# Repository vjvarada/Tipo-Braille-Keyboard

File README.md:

# What is a Braille KeyPad ?

- Braille KeyPad is a Bluetooth keyboard with a special layout that allows visually impaired individuals to easily navigate and type into SmartPhones and tablets. 
- There are 6 circular Braille input buttons on KeyPad arranged in a braille layout. By pressing combinations of the braille input buttons you can input text and symbols. Braille text input is compliant to UEB Grade 1 and Grade 2 braille except non-ASCII characters and some lower groupsigns & wordsigns.

# Physical Leyout:

- The braille keypads is a rectangular slab with rounded edges. It has all the buttons on one side, and is flat on the other.
- There is a slot for lanyard/wrist straps on one side of the rectangle. 
- Braille KeyPad consists of 6 circular "Braille" keys, 5 square "Special Keys" and a 5-Way Navigation stick with Center click.
- The 6 circular braille keys are used to input text and symbols by brailling in UEB grade 1 and grade 2 braille, in addition to long pressing the braille buttons of certain alphabets to trigger shortcuts on the SmartPhone/Tablet
- The 5 square keys are Alt, Ctrl, Shift, Space & Delete keys.
- The Navigation stick controls up, Down, Left, and Right.
- Clicking the center of the navigation stick represents enter/newline
- The bottom os the device has the ON/OFF slider and the USB Charging input.

# How to use
- Braille KeyPad is held between your palms, with the buttons facing away, and the flat side towards you. 

# Implementation:
How the HID Keypad is implemented for use with Braille

## Grade 1 Braille
The Braille Alphabet—Internationally Standardised
The letters a-z are common and standard for most braille country tables.

Grade 1 braille is a letter-for-letter substitution of its printed counterpart. This is the preferred code for beginners because it allows people to get familiar with, and recognize different aspects of, the code while learning how to read braille. 

English grade 1 braille consists of the 26 standard letters of the alphabet as well as punctuation.
### Charecters

| CHARACTER   |      BRAILLE      |  BRAILLE DOT/BUTTON # |
|----------|:-------------:|------:|
| letter sign | ⠰ | 56|
| a |	    ⠁	    | 1 |
| b |	    ⠃	    | 12 |
| c |	    ⠉	    | 14 |
| d |	    ⠙	    | 145 |
| e |	    ⠑	    | 15 |
| f |	    ⠋	    | 124 |
| g |	    ⠛	    | 1245 |
| h |	    ⠓	    | 125 |
| i |	    ⠊	    | 24 |
| j |	    ⠚	    | 245 |
| k |	    ⠅	    | 13 |
| l |	    ⠇	    | 123 |
| m |	    ⠍	    | 134 |
| n |	    ⠝	    | 1345 |
| o |	    ⠕	    | 135 |
| p |	    ⠏	    | 1234 |
| q |	    ⠟	    | 12345 |
| r |	    ⠗	    |1235 |
| s |	    ⠎	    | 234 |
| t |	    ⠞	    | 2345 |
| u |	    ⠥	    | 136 |
| v |	    ⠧	    | 1236 |
| w |	    ⠺	    | 2456 | 
| x |	    ⠭	    | 1346 |
| y |	    ⠽	    | 13456 |
| z |	    ⠵	    | 1356 |

### Numbers

| CHARACTER   |      BRAILLE      |  BRAILLE DOT/BUTTON # |
|----------|:-------------:|------:|
| number indicator |	⠼ 	| 3456 |
| 1 | 	⠼⠁	| 3456 1 |
| 2 |	⠼⠃	| 3456 12 |
| 3 |	⠼⠉	| 3456 14 |
| 4 |	⠼⠙	| 3456 145 |
| 5 |	⠼⠑	| 3456 15 |
| 6 |	⠼⠋	| 3456 124 |
| 7 |	⠼⠛	| 3456 1245 |
| 8 |	⠼⠓	| 3456 125 |
| 9 |	⠼⠊	| 3456 24 |
| 0 |	⠼⠚	| 3456 245 |

The number indicator (⠼) is placed before the first digit in a group. Space, hyphen, grade 1 indicator or clears it

Example:
```
100: 	⠼⠁⠚⠚

using Grade 1 indicator/Letter sign (⠰) to specify end of number
221b:	⠼⠃⠃⠁⠰⠃

```

### Punctuation

| CHARACTER   |      BRAILLE      |  BRAILLE DOT/BUTTON # |
|----------|:-------------:|------:|
|,|                     ⠂   |2|
|;|                  	⠆   |23|
|:|                    	⠒   |25|
|.(Period)|             ⠲   |256|
|?|     	            ⠦   |236|
|!|                     ⠖   |235|
|apostrophe '|          ⠄   |3|
|quote " |              ⠴   |356|
|hyphen - |             ⠤   |36|

### Symbols

| CHARACTER   |      BRAILLE      |  BRAILLE DOT/BUTTON # |
|----------|:-------------:|------:|
| & |	                 ⠈⠯	    | 4 12346|
| * |	                 ⠐⠔	    | 5 35|
| # |                    ⠸⠹        | 456 1456|
| @	|                    ⠈⠁        | 4 1|
| %	|                    ⠨⠴	    | 46 356|
| +	|                    ⠐⠖	    | 5 235|
| − (minus) |            ⠐⠤	    | 5 36|
| =	|                    ⠐⠶	    | 5 2356|
| ~ |                    ⠈⠔        | 4 35 |
| ` |                    ⠘⠡        | 45 16
| ^ |                    ⠈⠢        |4 26 |
| Underscore _ |         ⠨⠤        |46 36|
| Verical Line |         ⠸⠳        |456 1256| 
| / |                    ⠸⠌        |456 34|
| \ |                    ⠸⠡        |456 16|
| ( |                    ⠐⠣        |5 126|
| ) |                    ⠐⠜        |5 345|
| [ |                    ⠨⠣        |46 126|
| ] |                    ⠨⠜        |46 345|
| { |                    ⠸⠣        |456 126|
| } |                    ⠸⠜        |456 345|
| < |                    ⠈⠣        |4 126|
| > |                    ⠈⠜        |4 345|
| $ |                    ⠈⠎        |4 234 |
| " |                    ⠠⠶        |6 2346 |

### Indicators

| CHARACTER   |      BRAILLE      |  BRAILLE DOT/BUTTON # |
|----------|:-------------:|------:|
| number indicator |                	⠼    	| 3456 |
| grade 1 letter indicator |           ⠰	    | 56|
| grade 1 word indicator |             ⠰⠰	    | 56 56|
| grade 1 lock indicator |             ⠰⠰⠰	    | 56 56|
| grade 1 terminator indicator |       ⠰⠄	    | 56 3|
| capital letter indicator |           ⠠	    | 6|
| capital word indicator |             ⠠⠠      | 6 6|
| capital lock indicator |             ⠠⠠⠠     | 6 6 6|
| capital terminator indicator |       ⠠⠄      | 6 3|

```
The capital(ization) sign ⠠ marks the first letter of a word as capitalized. 
It may occur in the middle of a word for camel case, as in the name deAngelo. 
It is doubled to place a word in all caps; this must be repeated for each word of an all-cap text.
Use ⠠⠠ to Capitalise proceeding charecter, ⠠⠠ to Capitalise a full word,
⠠⠠⠠ to capitalise a full passage and ⠠⠄ to terminate. Using space/hyphen 
etc resets to normal unless not using paragraph caps. 
Warning: ⠠⠺⠁⠗⠝⠊⠝⠛
WARNING: ⠠⠠⠺⠁⠗⠝⠊⠝⠛
```

```
Note: The letter sign (grade 1 symbol indicator) ⠰ is used to force the end of a series of numbers.
For example, ⠙⠁ ⟨da⟩ preceded by a number sign, ⠼⠙⠁, is read as 41. 
If instead 4a is intended (as in a section or apartment number), 
then the letter sign is used to force a reading of a rather than 1 for the final character: ⠼⠙⠰⠁ ⟨4a⟩.

It is also used to mark a character as standing for a letter rather than for a word. For example, ⠃ ⟨b⟩ on its own is normally read as the word but;
to indicate that it is instead the letter b, the letter sign is used: ⠰⠃ b. Plurals of letters (mind your ps and qs)
always use an apostrophe in braille, but other derivations may not, as in ⠰⠝⠹ nth [time]: ⠠⠎⠬ is Sing, ⠰⠠⠎⠬ is S-ing/Essing. The letter sign is also used to mark lower-case Roman numbers, as in ⠰⠊⠊⠊ ⟨iii⟩.
 ```
## Grade 2 Braille 

The literary braille code, grade 2, uses “contractions” that substitute shorter sequences for the full spelling of commonly-occurring letter groups. The contractions are similar to English print contractions, like “cannot” versus “can’t”, in the way that a word is shortened. For example, “the” is usually a single character in braille. 
Grade 2 braille is the most commonly used form of braille code and is found in books, public signage, and restaurant menus to name a few. It consists of the 26 standard letters of the alphabet, punctuation, and contractions.

```
letter sign  (⠰) used to mark a character as standing for a letter rather than for a word. For example,
 ⠃ ⟨b⟩ on its own is normally read as the word but; to indicate that it is instead the letter b, 
the letter sign is used: ⠰⠃ b. Plurals of letters (mind your ps and qs) always use an apostrophe in braille,
but other derivations may not, as in ⠰⠝⠹ nth [time]: ⠠⠎⠬ is Sing, ⠰⠠⠎⠬ is S-ing/Essing.[27] The letter sign 
is also used to mark lower-case Roman numbers, as in ⠰⠊⠊⠊ ⟨iii⟩.
```
### Alphabetic Wordsigns

| CHARACTER   | WORD    |      BRAILLE      |  BRAILLE DOT/BUTTON # |
|----------|:-------------:|:-------------:|------:|
| b | but |	            ⠃	    | 12 |
| c | can |	            ⠉	    | 14 |
| d | do |	            ⠙	    | 145 |
| e | every|            ⠑	    | 15 |
| f | from |            ⠋	    | 124 |
| g | go |              ⠛	    | 1245 |
| h | have |            ⠓	    | 125 |
| j | just |            ⠚	    | 245 |
| k | knowledge |	    ⠅	    | 13 |
| l | like |	        ⠇	    | 123 |
| m | more |	        ⠍	    | 134 |
| n | not |	            ⠝	    | 1345 |
| p | people |	        ⠏	    | 1234 |
| q | quite |	        ⠟	    | 12345 |
| r | rather |	        ⠗	    |1235 |
| s | so |	            ⠎	    | 234 |
| t | that |	        ⠞	    | 2345 |
| u | us |	            ⠥	    | 136 |
| v | very |	        ⠧	    | 1236 |
| w | will |	        ⠺	    | 2456 | 
| x | it |	            ⠭	    | 1346 |
| y | you |	            ⠽	    | 13456 |
| z | as |	            ⠵	    | 1356 |

### Strong Contractions (Part and Whole Word)

| CHARACTER   |      BRAILLE      |  BRAILLE DOT/BUTTON # |
|----------|:-------------:|------:|
| and |	    ⠯	    | 12346 |
| for |	    ⠿	    | 123456 |
| of |	    ⠷	    | 12356 |
| the |	    ⠮	    | 2346 |
| with |    ⠾	    | 23456 |

### Strong Wordsigns

| CHARACTER   |      BRAILLE      |  BRAILLE DOT/BUTTON # |
|----------|:-------------:|------:|
| child |	    ⠡	    | 16 |
| shall |	    ⠩	    | 146 |
| this |	    ⠹	    | 1456 |
| which |	    ⠱	    | 156 |
| out |	        ⠳	    | 1256 |
| still |	    ⠌	    | 34 |

isStandingAlone?

### Strong Groupsigns

| CHARACTER   |      BRAILLE      |  BRAILLE DOT/BUTTON # | Note |
|----------|:-------------:|:------:|------:|
| -ch- |	    ⠡	    | 16 | Letter join on either side|
| -sh- |	    ⠩	    | 146 |Letter join on either side|
| -th- |        ⠹	    | 1456 |Letter join on either side|
| -wh- |	    ⠱	    | 156 |Letter join on either side|
| -ou- |	    ⠳	    | 1256 |Letter join on either side|
| -st- |	    ⠌	    | 34 |Letter join on either side|
|------|----------------|----| -------------------------|
| gh |	        ⠣	    | 126 |
| ed |	        ⠫	    | 1246 |
| er |	        ⠻	    | 12456 |
| ow |          ⠪	    | 246 |
| ar |  	    ⠜	    | 345 |
| -ing |	    ⠬	    | 346 |Letter join on one side only, cannot be used to start a word|

### Lower Groupsigns

| CHARACTER   |      BRAILLE      |  BRAILLE DOT/BUTTON # | Note |
|----------|:-------------:|:------:|------:|
| -ea- |      ⠂	    | 2|Letters join on both side|
| -bb- |      ⠆	    | 23 |Letters join on both side|
| -cc- |      ⠒	    | 25 |Letters join on both side|
| -ff- |	  ⠖	    | 235 |Letters join on both side|
| -gg- |      ⠶	    | 2356 |Letters join on both side|
|------|----------------|----| -------------------------|
| be- |	      ⠆	    | 23 | |
| con- |	  ⠒	    | 25 |Letters join on one side only |
| dis- |	  ⠲	    | 256 |Letters join on one side only |
| -en- |	  ⠢	    | 26 |Letter join on either side|
| in |	      ⠔	    | 35 | |

### Lower Wordsigns

| CHARACTER   |      BRAILLE      |  BRAILLE DOT/BUTTON # |
|----------|:-------------:|------:|
| be |      ⠆	    | 23 |
| enough |  ⠢	    | 26 |
| were |    ⠶	    | 2356 |
| his |	    ⠦	    | 236 |
| in |	    ⠔	    | 35 |
| was |	    ⠴	    | 356 |

### Initial Letter Contractions

| CHARACTER   |      BRAILLE      |  BRAILLE DOT/BUTTON # |
|----------|:-------------:|------:|
|    day |  |5 145
|   ever |  |5 15
|  father | |5 124
|    here | |5 125
|    know | |5 13
|    lord | |5 123
|    mother |   |5 134
|    name | |5 1345
|    one |  |5 135
|    part | |5 1234
|    question | |5 12345
|    right |    |5 1235
|    some | |5 234
|    time | |5 2345
|    under | |5 136
|    work | |5 2456
|    young | |5 13456
|    there | |5 2346
|    character | |5 16
|    through | |5 1456
|    where | |5 156
|    ought | |5 1256
|    upon | |45 136
|    word | |45 2456
|    these | |45 2346
|    those | |45 1456
|    whose | |45 156
|    cannot | |456 14
|    had | |456 125
|    many | |456 134
|    spirit | |456 234
|    world | |456 2456
|    their | |456 2346

### final Letter Groupsigns

| CHARACTER   |      BRAILLE      |  BRAILLE DOT/BUTTON # |
|----------|:-------------:|------:|
|ound| | 46 145 |
|ance| | 46 15 |
|sion| | 46 1345 |
|less| | 46 234|
|ount| | 46 2345|
|ence| | 56 15|
|ong| | 56 1245|
|ful| | 56 123|
|tion| | 56 1345|
|ness| | 56 234|
|ment| | 56 2345|
|ity| | 56 13456|

## Talkback Basics

|Key Combo      |   Action | 
|:----------|------:|
| Hold z | Pause/Resume Talkback | 
| Alt + Space | Open Talkback Menu | 

## Item Navigation controls

|Key Combo      |   Action | 
|:----------|------:|
| Alt + Left  | Navigate to the next item|
| Alt + Right  | Navigate to the previous item |
| Alt + Up | Navigate to the item above |
| Alt + Down | Navigate to the item below|
|_________|________|
| Alt + Ctrl + Left | Navigate to First Item |
| Alt + Ctrl + Right | Navigate to Last Item |
| Alt + Ctrl + Down  | Navigate to Next Window |
| Alt + Ctrl + Up | Navigate to Previous Window |
|_________|________|
| Alt + Enter | Select an item |
| Alt + Shift + Enter |Long press | 

## Text Editing  
|Key Combo      |   Action | 
|:----------|------:|
| Right | Move cursor right |
| Left | Move cursor left |
| Up | Move cursor to line above |
| Down | Move cursor to line below |
| Ctrl + Right | Move cursor to Previous Word |
| Ctrl + Left | Move Cursor to Next Word |
| Shift + Right | Select next character |
| Shift + Left | Select Previous Character |
| Shift + Up | Select Line Above |
| Shift + Down | Select Line Below |
| Shift + Ctrl + Left | Select Previous Word |
| Shift + Ctrl + Right | Select Next Word |

## Reading controls

|Key Combo      |   Action | 
|:----------|------:|
| Alt + Shift + Control + Up/Down | Cycle Reading Controls | 
| Alt + Shift + Up/Down | Go to Next/Prev as per reading Controls |
| Alt + Shift + Right  | Navigate to Next Character |
| Alt  + Shift + Left |  Navigate to Previous Character |
| Alt + Ctrl + Shift + Right | Navigate to Next Word |
| Alt + Ctrl + Shift + Left |  Navigate to Previous Word |

## Continuous Reading controls

|Key Combo      |   Action | 
|:----------|------:|
| Alt + Ctrl + Enter | Continuous read from top |
| Alt + Ctrl + Shift + Enter | Continuous read from Next Item |
| Alt + Right  | Fast-forwards the text.|
| Alt + Left | Rewinds the text. |
| Enter | Stop Continuous Reading |

## Slider Controls  

|Key Combo      |   Action | 
|:----------|------:|
| Alt + Shift + Up | Increase Slider Value|
| Alt + Shift + Down  | Decrease Slider Value |

## Alphabetic Shortcuts

Long press braille character to activate

| CHARACTER   |      Shortcut      |  Key Combo |
|----------|:-------------:|------:|
| a | Assistant | win |
| b | Back | alt + backspace |
| l | Apps List / Select All | Ctrl + a |
| c | Copy | ctrl + c |
| x | Cut | ctrl + x |
| v | Paste | ctrl + v |
| d | Maps | win + m |
| e | Email | win + e |
| h | Home | ctrl + alt + h |
| r | Recent apps | ctrl + alt + r |
| s | Music | win + p |
| m | Messages | win + s |
| n | notifications | ctrl + alt + n |
| f | Screen Search | ctrl + alt + / |
| p | Contacts | win + c |
| y | Youtube | win + y |
| t | Calender | win + l |

#### References:

1. Generate Markdwn tables from https://www.tablesgenerator.com/markdown_tables
2. Braille Code Referance: https://www.pharmabraille.com/braille-codes/unified-english-braille-ueb-code/
3. Test and understand using online braille translator: https://www.branah.com/braille-translator
4. Wikipedia entry https://en.wikipedia.org/wiki/English_Braille
5. http://www.dotlessbraille.org/brailleindicators.htm#markup
6. Android & TalkBack Mobile Accessibility Cheat Sheet https://pauljadam.com/demos/talkbackcheatsheet.html
7. Keyboard Shortcuts https://www.cnet.com/culture/keyboard-shortcuts-for-android-phones/
8. Talkback Shortcuts https://dequeuniversity.com/screenreaders/talkback-shortcuts
9. Braille to Binary encoder https://www.dcode.fr/braille-alphabet

# TIPO
Plug n Play Braille Keyboard for your smartphone
Shows up as a HID device, and behaves just like a Keyboard would.

## TIPO V1
USB HID only implementation using atmega32u4/Adruni Leonardo

## TIPO BLE

BLE HID implementation using ESP32

------------------------------------------------------------------
# Hardware Connections

## Architecture

## Button Map:

| Button | ESP32 Pin # |
| :------: | :-----------:|
| BTN1 | 25|
| BTN2 | 26|
| BTN3 | 27|
| BTN4 | 13|
| BTN5 | 15|
| BTN6 | 2 |
| BTN7 | 19|
| BTN8 | 18|
| BTN9 | 17|
| BTN10| 16|
| BTN11| 4 |
| CNT | 33|
| UP | 34 |
| DWN | 35|
| LFT | 36|
| RGT | 39|

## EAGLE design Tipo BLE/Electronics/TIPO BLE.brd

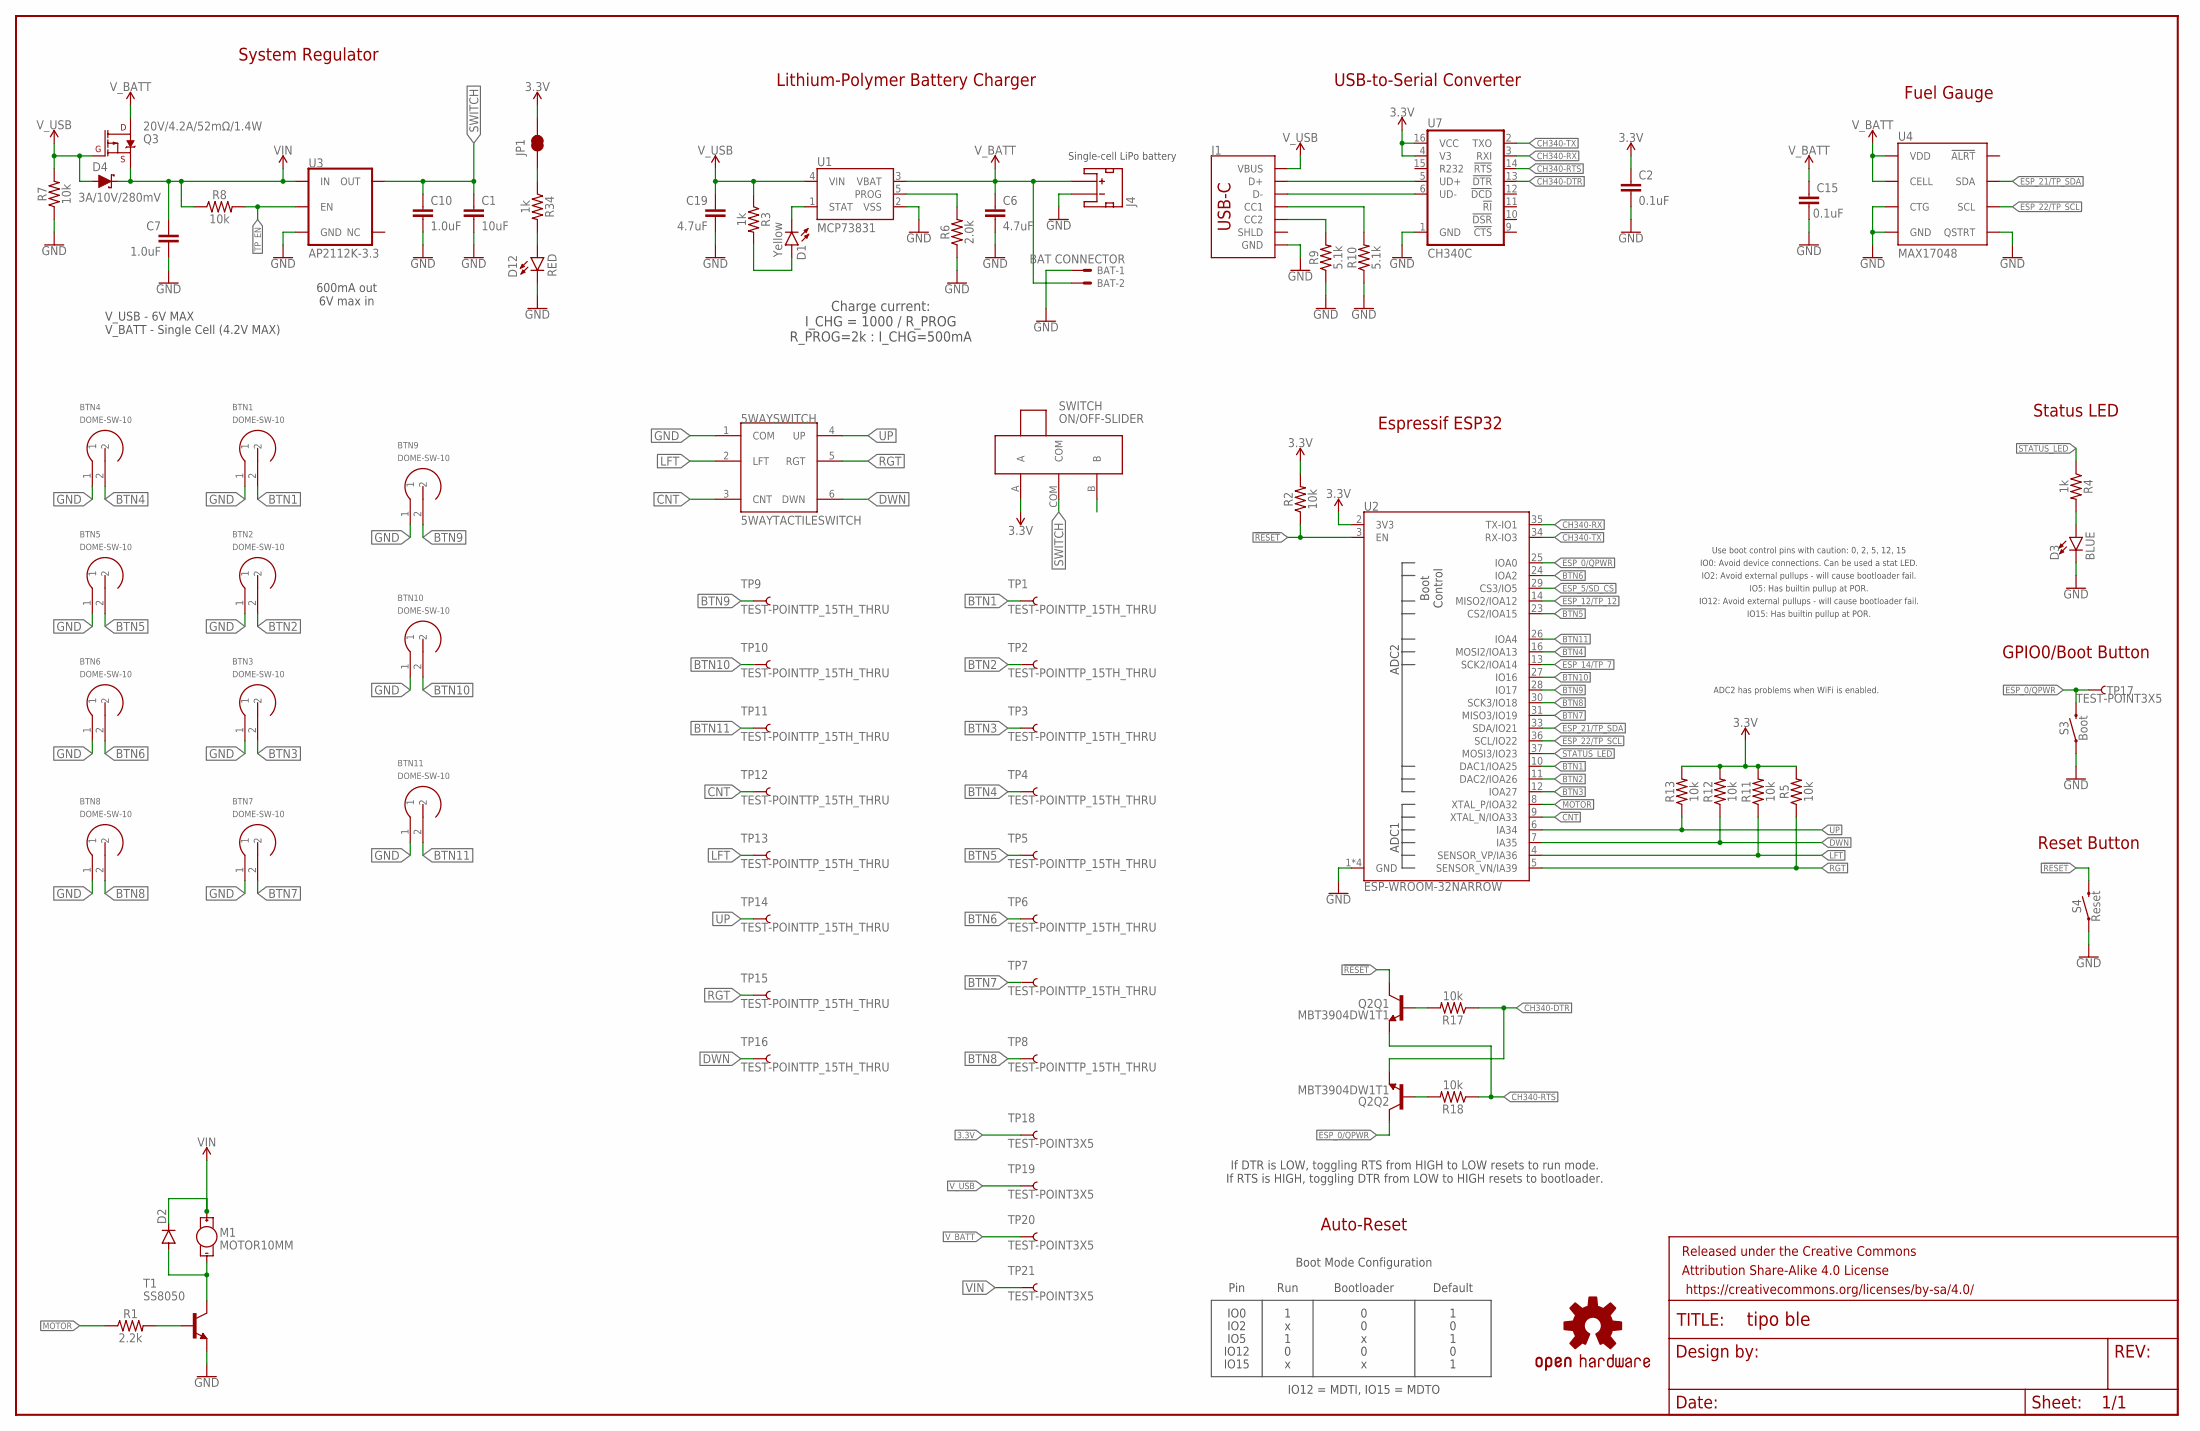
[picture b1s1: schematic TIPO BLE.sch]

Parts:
5WAYSWITCH: 5WAYTACTILESWITCH
BAT: BAT CONNECTOR; JST-XH-02-PACKAGE-LONG-PAD
BTN1, BTN2, BTN3, BTN4, BTN5, BTN6, BTN7, BTN8, BTN9, BTN10, BTN11: DOME-SW-10
C1: 10uF; 0402-TIGHT
C2, C15: 0.1uF; 0402-TIGHT
C6: 4.7uF; 0402-TIGHT
C7, C10: 1.0uF; 0402-TIGHT
C19: 4.7uF; 0603
D1: Yellow; LED-0603
D2: DIODE-DO-214AC; DO-214AC
D3: BLUE; LED-0603
D4: 3A/10V/280mV; SOD-323
D12: RED; LED-0603
FRAME1: FRAME-LEDGER; CREATIVE_COMMONS
J1: USB_C_2-LAYER_PADS; USB-C-16P-2LAYER-PADS
J4: JST_2MM_MALE; JST-2-SMD@1
JP1: JUMPER-SMT_2_NC_TRACE_SILK; SMT-JUMPER_2_NC_TRACE_SILK
LOGO1: OSHW-LOGOL; OSHW-LOGO-L
M1: MOTOR10MM; VIBE-MOTOR-10MM
Q2: MBT3904DW1T1; SC70-6
Q3: 20V/4.2A/52mΩ/1.4W; SOT23-3
R1: 2.2k; 0603
R2, R5, R7, R8, R11, R12, R13, R17, R18: 10k; 0402-TIGHT
R3, R4, R34: 1k; 0402-TIGHT
R6: 2.0k; 0603
R9, R10: 5.1k; 0402-TIGHT
S3: Boot; TACTILE_SWITCH_SMD_4.6X2.8MM
S4: Reset; TACTILE_SWITCH_SMD_4.6X2.8MM
SWITCH: ON/OFF-SLIDER
T1: SS8050; SOT23
TP1, TP2, TP3, TP4, TP5, TP6, TP7, TP8, TP9, TP10, TP11, TP12, TP13, TP14, TP15, TP16: TEST-POINTTP_15TH_THRU; TP_15TH
TP17, TP18, TP19, TP20, TP21: TEST-POINT3X5; PAD.03X.05
U1: MCP73831; SOT23-5
U2: ESP-WROOM-32NARROW; ESP-WROOM-32-NARROW
U3: AP2112K-3.3; SOT23-5
U4: MAX17048; DFN-8
U7: CH340C; SO016

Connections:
3.3V: C2.1, JP1.2, R2.2, R5.2, R11.2, R12.2, R13.2, SWITCH.A, TP18.1, U2.2 (3V3), U7.4 (V3), U7.16 (VCC)
!RESET!: Q2.3 (C), R2.1, S4.3 (2), S4.4 (2), U2.3 (EN)
BTN1: BTN1.2, TP1.1, U2.10 (DAC1/IOA25)
BTN2: BTN2.2, TP2.1, U2.11 (DAC2/IOA26)
BTN3: BTN3.2, TP3.1, U2.12 (IOA27)
BTN4: BTN4.2, TP4.1, U2.16 (MOSI2/IOA13)
BTN5: BTN5.2, TP5.1, U2.23 (CS2/IOA15)
BTN6: BTN6.2, TP6.1, U2.24 (IOA2)
BTN7: BTN7.2, TP7.1, U2.31 (MISO3/IO19)
BTN8: BTN8.2, TP8.1, U2.30 (SCK3/IO18)
BTN9: BTN9.2, TP9.1, U2.28 (IO17)
BTN10: BTN10.2, TP10.1, U2.27 (IO16)
BTN11: BTN11.2, TP11.1, U2.26 (IOA4)
CH340-DTR: Q2.1 (E), R17.1, U7.13 (!DTR)
CH340-RTS: Q2.4 (E), R18.1, U7.14 (!RTS)
CH340-RX: U2.35 (TX-IO1), U7.3 (RXI)
CH340-TX: U2.34 (RX-IO3), U7.2 (TXO)
CHG: D1.C, U1.1 (STAT)
CHG_LED: D1.A, R3.2
CNT: 5WAYSWITCH.3 (CNT), TP12.1, U2.9 (XTAL_N/IOA33)
D+: J1.A6 (D+), J1.B6 (D+), U7.5 (UD+)
D-: J1.A7 (D-), J1.B7 (D-), U7.6 (UD-)
DTR-10K: Q2.5 (B), R17.2
DWN: 5WAYSWITCH.6 (DWN), R12.1, TP16.1, U2.7 (IA35)
ESP_0/QPWR: Q2.6 (C), S3.3 (2), S3.4 (2), TP17.1, U2.25 (IOA0)
ESP_5/SD_CS: U2.29 (CS3/IO5)
ESP_12/TP_12: U2.14 (MISO2/IOA12)
ESP_14/TP_7: U2.13 (SCK2/IOA14)
ESP_21/TP_SDA: U2.33 (SDA/IO21), U4.8 (SDA)
ESP_22/TP_SCL: U2.36 (SCL/IO22), U4.7 (SCL)
GND: 5WAYSWITCH.1 (COM), BAT.1, BTN1.1, BTN2.1, BTN3.1, BTN4.1, BTN5.1, BTN6.1, BTN7.1, BTN8.1, BTN9.1, BTN10.1, BTN11.1, C1.2, C2.2, C6.2, C7.2, C10.2, C15.2, C19.2, D3.C, D12.C, J1.GND, J1.GND2 (GND), J4.1 (-), R6.1, R7.1, R9.1, R10.1, S3.1, S3.2 (1), S4.1, S4.2 (1), T1.2 (E), U1.2 (VSS), U2.1 (GND), U2.15 (GND), U2.38 (GND), U2.GND, U3.2 (GND), U4.1 (CTG), U4.4 (GND), U4.6 (QSTRT), U4.9 (GND), U7.1 (GND)
LFT: 5WAYSWITCH.2 (LFT), R11.1, TP13.1, U2.4 (SENSOR_VP/IA36)
MOTOR: R1.1, U2.8 (XTAL_P/IOA32)
unnamed: R1.2, T1.1 (B)
unnamed: D2.A, M1.-, T1.3 (C)
unnamed: JP1.1, R34.1
unnamed: J1.B5 (CC2), R9.2
unnamed: J1.A5 (CC1), R10.2
unnamed: D3.A, R4.2
unnamed: R6.2, U1.5 (PROG)
unnamed: D12.A, R34.2
RGT: 5WAYSWITCH.5 (RGT), R5.1, TP15.1, U2.5 (SENSOR_VN/IA39)
RTS-10K: Q2.2 (B), R18.2
STATUS_LED: R4.1, U2.37 (MOSI3/IO23)
SWITCH: C1.1, C10.1, SWITCH.COM, U3.5 (OUT)
TP_EN: R8.2, U3.3 (EN)
UP: 5WAYSWITCH.4 (UP), R13.1, TP14.1, U2.6 (IA34)
VIN: C7.1, D2.C, D4.C, M1.+, Q3.2 (S), R8.1, TP21.1, U3.1 (IN)
V_BATT: BAT.2, C6.1, C15.1, J4.2 (+), Q3.3 (D), TP20.1, U1.3 (VBAT), U4.2 (CELL), U4.3 (VDD)
V_USB: C19.1, D4.A, J1.VBUS1 (VBUS), J1.VBUS2 (VBUS), Q3.1 (G), R3.1, R7.2, TP19.1, U1.4 (VIN)

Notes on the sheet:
System Regulator
600mA out 6V max in
V_USB - 6V MAX V_BATT - Single Cell (4.2V MAX)
Single-cell LiPo battery
Charge current: I_CHG = 1000 / R_PROG R_PROG=2k : I_CHG=500mA
Lithium-Polymer Battery Charger
USB-to-Serial Converter
Fuel Gauge
Reset Button
Status LED
GPIO0/Boot Button
Auto-Reset
Espressif ESP32
If DTR is LOW, toggling RTS from HIGH to LOW resets to run mode. If RTS is HIGH, toggling DTR from LOW to HIGH resets to bootloader.
Pin
IO0
IO2
IO12
IO15
IO5
Run
Bootloader
Default
IO12 = MDTI, IO15 = MDTO
Boot Mode Configuration
IO0: Avoid device connections. Can be used a stat LED.
ADC2 has problems when WiFi is enabled.
IO12: Avoid external pullups - will cause bootloader fail.
Use boot control pins with caution: 0, 2, 5, 12, 15
IO2: Avoid external pullups - will cause bootloader fail.
IO15: Has builtin pullup at POR.
IO5: Has builtin pullup at POR.

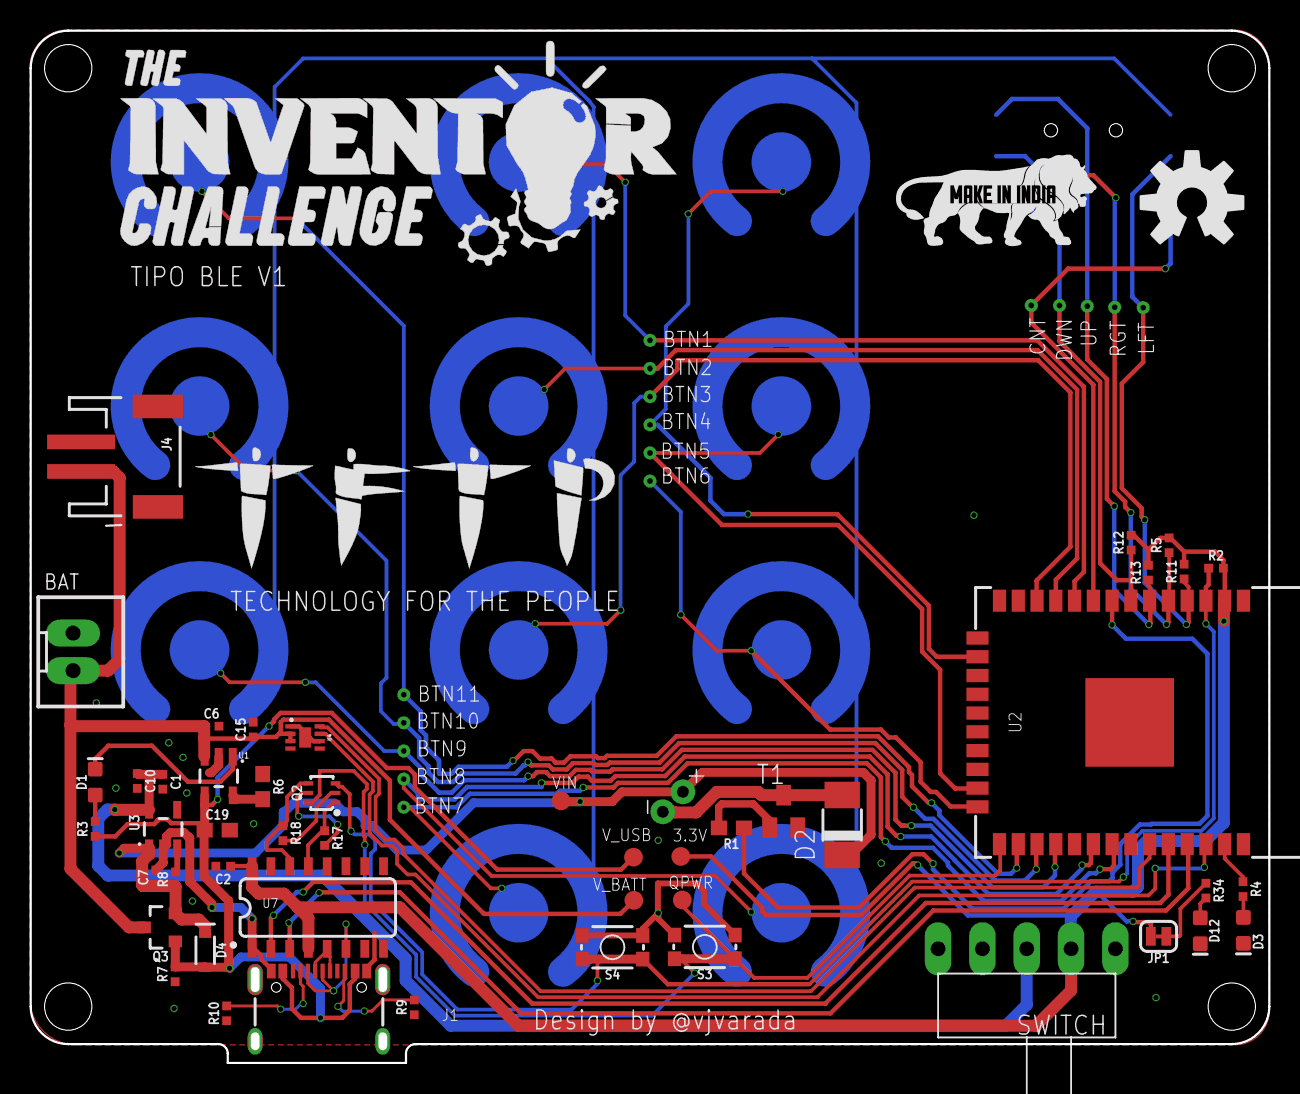
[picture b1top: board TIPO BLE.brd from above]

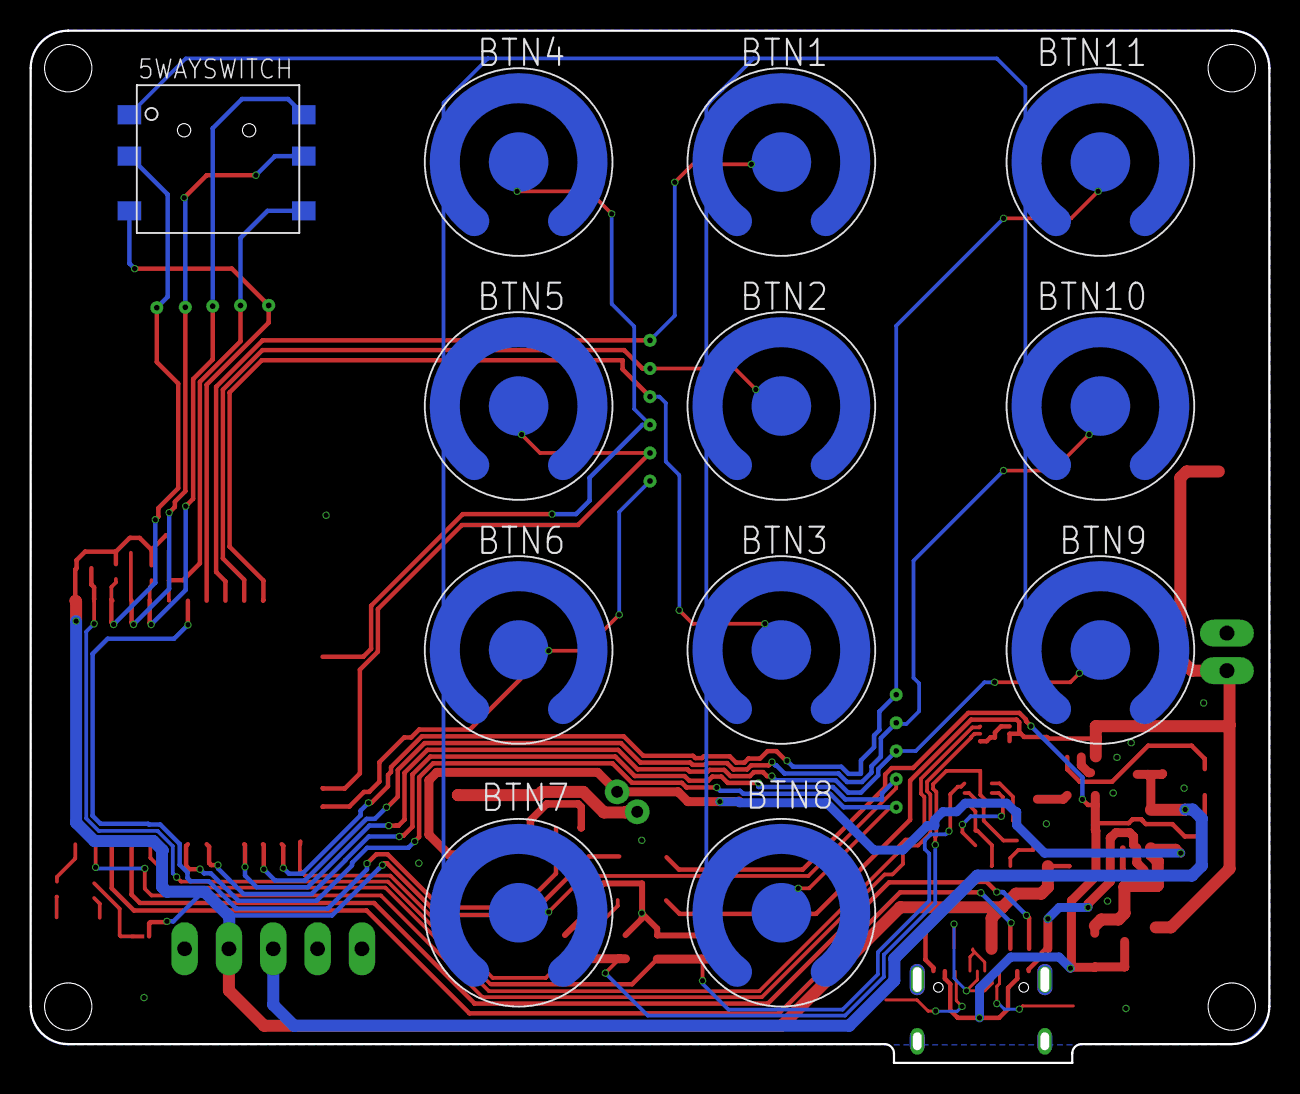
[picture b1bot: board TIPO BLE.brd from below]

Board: 2 copper layers, 83.8 x 69.8 mm, 82 parts (28 on the bottom side), 47 nets.

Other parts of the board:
U$1: TFTPLOGO
U$2: INVENTORCHALLENGE
U$3: MAKEININDIA

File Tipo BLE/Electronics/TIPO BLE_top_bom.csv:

Comment,Designator,Footprint,LCSC Part #
C95872,D2,DO-214AC,
918-418K2023S40001,J1,USB-C-16P-2LAYER-PADS,
0.1uF,C2 C15,0402-TIGHT,
1.0uF,C7 C10,0402-TIGHT,
1k,R3 R4 R34,0402-TIGHT,
2.0k,R6,603,
2.2k,R1,603,
3A/10V/280mV,D4,SOD-323,
4.7uF,C6,0402-TIGHT,
4.7uF,C19,603,
5.1k,R9 R10,0402-TIGHT,
10k,R2 R5 R7 R8 R11 R12 R13 R17 R18,0402-TIGHT,
10uF,C1,0402-TIGHT,
20V/4.2A/52mΩ/1.4W,Q3,SOT23-3,
AP2112K-3.3,U3,SOT23-5,
BLUE,D3,LED-0603,
Boot,S3,TACTILE_SWITCH_SMD_4.6X2.8MM,
CH340C,U7,SO016,
ESP-WROOM-32NARROW,U2,ESP-WROOM-32-NARROW,
MAX17048,U4,DFN-8,
MBT3904DW1T1,Q2,SC70-6,
MCP73831,U1,SOT23-5,
RED,D12,LED-0603,
Reset,S4,TACTILE_SWITCH_SMD_4.6X2.8MM,
SS8050,T1,SOT23,
Yellow,D1,LED-0603,

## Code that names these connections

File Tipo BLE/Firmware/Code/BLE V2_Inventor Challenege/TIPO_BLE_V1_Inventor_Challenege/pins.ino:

#define BTN1 22 
#define BTN2 25
#define BTN3 14
#define BTN4 19
#define BTN5 26
#define BTN6 27
#define BTN7 13
#define BTN8 12
#define BTN9 32
#define BTN10 33
#define BTN11 39
#define CNT 15
#define UP 16
#define DWN 2
#define RGT 17
#define LFT 4

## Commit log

2020-02-25 added comments and example code
2022-06-18 Synced local changes
2022-06-22 Synced CAD parts
2022-06-22 System Architecture
2022-06-22 Tipo V2 Hardware Architecture
2022-06-22 Added Tipo V2 Hardware Architecture
2022-06-23 changed filename
2022-06-27 Organized the folder
2022-06-27 Documentation
2022-06-27 Updated Documentation
2022-07-02 Added Tipo V2 Hardware Architeture.drawio.png
2022-07-02 Documentation Updated
2022-07-07 Synced board files, updated documentation
2022-07-07 Fixed silk screen on bottom layer
2022-07-08 Files updated, Working code
2022-07-09 Code updates
2022-07-11 code and documenatation changed
2022-07-14 started working on grade 2
2022-07-19 Grade 2 contractions implemented
2022-07-21 Documtantation
2022-07-23 documenation
2022-08-17 Changes made
2023-02-01 Made change for NIDHI PRAYAS
2023-02-01 Niidhi Prayas

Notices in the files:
parts and their libraries:
SparkFun-Connectors: Licensing: Creative Commons ShareAlike 4.0 International - https://creativecommons.org/licenses/by-sa/4.0
SparkFun-Aesthetics: Released under the Creative Commons Attribution Share-Alike 4.0 License
SparkFun-Aesthetics: https://creativecommons.org/licenses/by-sa/4.0
